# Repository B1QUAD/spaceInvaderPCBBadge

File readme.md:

# spaceInvaderPCBBadge  
A fun and simple PCB badge made using an ATTINY85 microcontroller and some LEDs.  
Here is the schematic:  

Here is the PCB layout:

Some 3D renders of the circuit board:

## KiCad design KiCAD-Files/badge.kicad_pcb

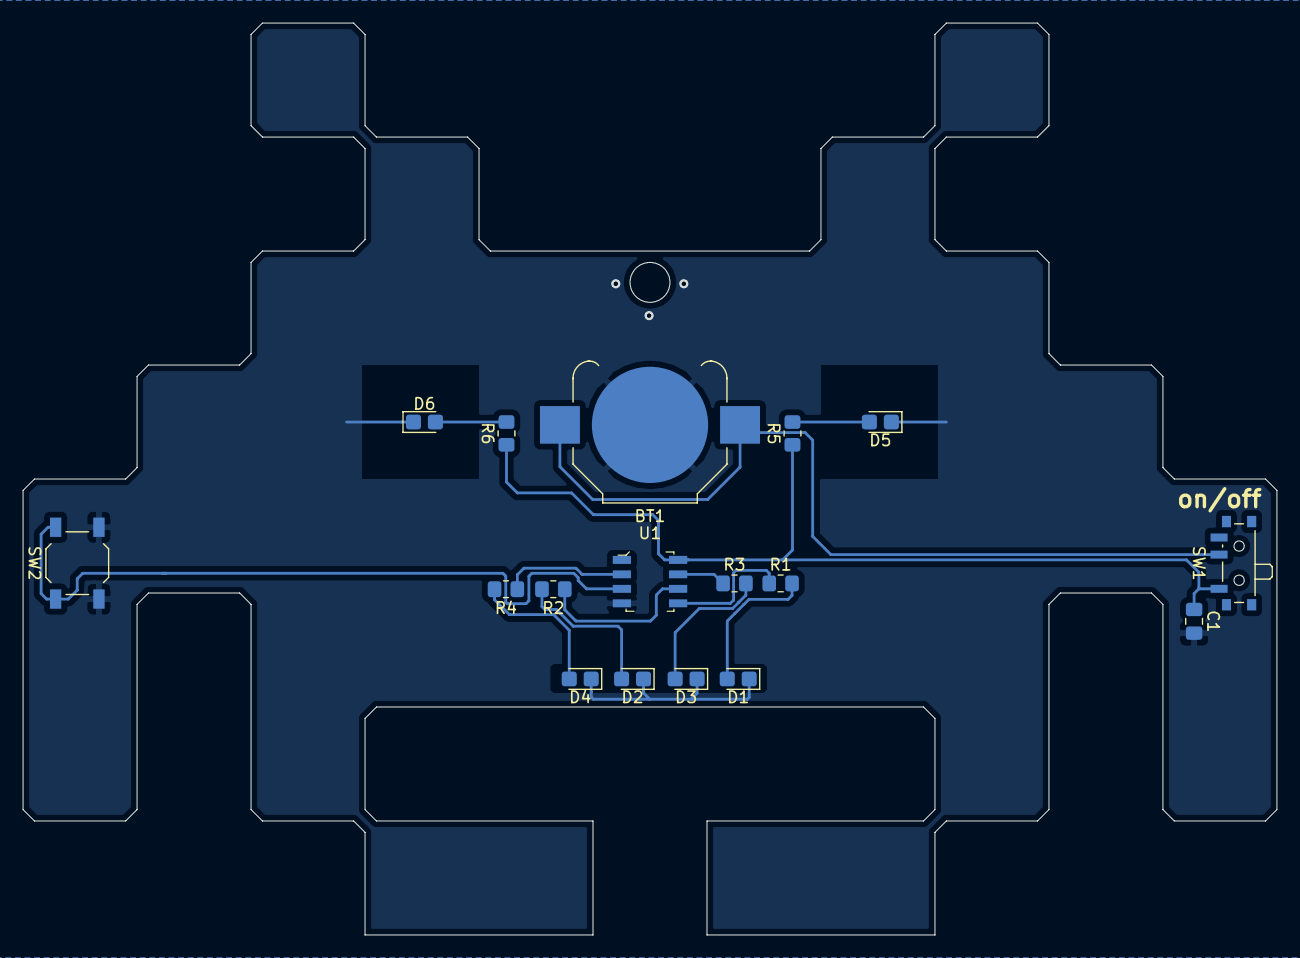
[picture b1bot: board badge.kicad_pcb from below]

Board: 2 copper layers, 110.0 x 80.0 mm, 17 parts (17 on the bottom side), 14 nets.

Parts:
BT1: Battery_Cell; BatteryHolder_Keystone_3000_1x12mm
C1: C_Small; C_0805_2012Metric_Pad1.18x1.45mm_HandSolder
D1, D2, D3, D4, D5, D6: LED; LED_0805_2012Metric_Castellated
R1, R2, R3, R4, R5, R6: 330; R_0805_2012Metric_Pad1.20x1.40mm_HandSolder
SW1: SW_SPDT; SW_SPDT_PCM12
SW2: SW_Push; SW_SPST_TL3342
U1: ATTINY85-20SU; SOIC-8_W5.3mm

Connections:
+3V3: BT1.1, SW1.2
GND: BT1.2, C1.2, D1.1, D2.1, D3.1, D4.1, D5.1, D6.1, SW2.2, U1.4
unnamed: D1.2, R1.2
unnamed: D2.2, R2.2
unnamed: D3.2, R3.2
unnamed: D4.2, R4.2
unnamed: D5.2, R5.2
unnamed: D6.2, R6.2
VCC: C1.1, R5.1, R6.1, SW1.1, U1.8
button: SW2.1, U1.3
led1: R1.1, U1.5
led2: R2.1, U1.6
led3: R3.1, U1.7
led4: R4.1, U1.2

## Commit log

2021-03-22 Fixed readme image URLs
2021-03-22 Fixed readme image URLs, attempt #2
2021-03-22 The images keep breaking
2021-03-22 MFW the whole problem was that I typed github as gihub /_-
2021-03-25 Added license
